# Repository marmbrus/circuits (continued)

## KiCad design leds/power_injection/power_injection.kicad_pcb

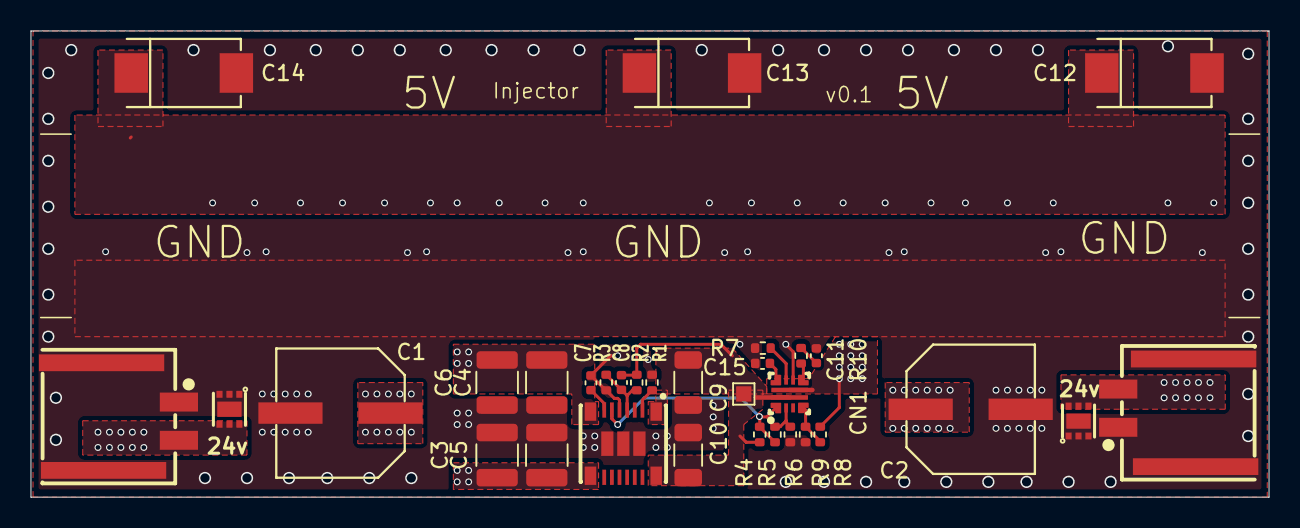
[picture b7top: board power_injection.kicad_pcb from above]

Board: 4 copper layers, 81.0 x 30.5 mm, 32 parts (0 on the bottom side), 14 nets.

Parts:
C1, C2: 220uF; CAP-SMD_BD8.0-L8.3-W8.3-FD
C3, C4, C5, C6: 10uF; C_1210_3225Metric
C7: 47nF; C_0402_1005Metric
C8: 47pF; C_0402_1005Metric
C9, C10: 10uF; C_1206_3216Metric
C11: 100nF; C_0402_1005Metric
C12, C13, C14: 330uF; CAP-SMD_L7.3-W4.3-FD
C15: 15nF; C_0402_1005Metric
CN1, CN2: 105430-1102; CONN-SMD_2P-P2.54_105430-1102
D5, D6: TVS2700DRVR; WSON-6_L2.0-W2.0-P0.65-BL-EP
R1: 162k; R_0402_1005Metric
R2: 73.2k; R_0402_1005Metric
R3: 10k; R_0402_1005Metric
R4: 470k; R_0402_1005Metric
R5: 45.3k; R_0402_1005Metric
R6: 147k; R_0402_1005Metric
R7: 562; R_0402_1005Metric
R8: 100k; R_0402_1005Metric
R9: 34k; R_0402_1005Metric
R10: 100; R_0402_1005Metric
TP1: TestPoint; TestPoint_Pad_1.0x1.0mm
U1: TPSM86837RCGR; B3QFN-19_L5.5-W5.0-P0.50-TL
U2: TPS259474LRPWR; VQFN-10_L2.0-W2.0-P0.45-TL

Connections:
/NanoFitPower/VIN: C1.1, C2.1, C3.1, C4.1, C5.1, C6.1, CN1.2, CN2.2, D5.4 (IN), D5.5 (IN), D5.6 (IN), D6.4 (IN), D6.5 (IN), D6.6 (IN), U1.8 (VIN), U1.9 (VIN)
/buck24v/5V_RAW: C8.1, C9.1, C10.1, R2.1, R4.1, TP1.1, U1.1 (VOUT), U1.16 (VOUT), U2.5 (IN)
/buck24v/VOUT: C12.1, C13.1, C14.1, R8.1, U2.6 (OUT)
GND: C1.2, C2.2, C3.2, C4.2, C5.2, C6.2, C7.2, C9.2, C10.2, C11.2, C12.2, C13.2, C14.2, C15.2, CN1.1, CN1.3, CN1.4, CN2.1, CN2.3, CN2.4, D5.1 (GND), D5.2 (GND), D5.3 (GND), D5.7 (GND), D6.1 (GND), D6.2 (GND), D6.3 (GND), D6.7 (GND), R1.2, R3.2, R6.2, R7.2, R9.2, U1.5 (AGND), U1.17 (PGND), U1.18 (PGND), U1.19 (PGND), U2.8 (GND)
unnamed: C11.1, R10.2
unnamed: C8.2, R2.2, R3.1, U1.4 (FB)
unnamed: R1.1, U1.2 (MODE)
unnamed: R4.2, R5.1, U1.6 (PG), U2.1 (EN/UVLO)
unnamed: C7.1, U1.7 (SS)
unnamed: R10.1, U2.7 (DVDT)
unnamed: R7.1, U2.9 (ILM)
unnamed: C15.1, U2.10 (ITIMER)
unnamed: R5.2, R6.1, U2.2 (OVLO/OVCSEL)
unnamed: R8.2, R9.1, U2.4 (PGTH/~FLT)

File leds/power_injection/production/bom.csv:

Designator,Footprint,Quantity,Value,LCSC Part #
"C1, C2",CAP-SMD_BD8.0-L8.3-W8.3-FD,2,220uF,C2923769
"C10, C9",1206,2,10uF,C2803389
C11,0402,1,100nF,
"C12, C13, C14",CAP-SMD_L7.3-W4.3-FD,3,330uF,C2159214
C15,0402,1,15nF,
"C3, C4, C5, C6",1210,4,10uF,C77102
C7,0402,1,47nF,
C8,0402,1,47pF,
"CN1, CN2",CONN-SMD_2P-P2.54_105430-1102,2,105430-1102,C2976139
"D5, D6",WSON-6_L2.0-W2.0-P0.65-BL-EP,2,TVS2700DRVR,C523797
R1,0402,1,162k,
R10,0402,1,100,
R2,0402,1,73.2k,
R3,0402,1,10k,
R4,0402,1,470k,
R5,0402,1,45.3k,
R6,0402,1,147k,
R7,0402,1,562,
R8,0402,1,100k,
R9,0402,1,34k,
TP1,TestPoint_Pad_1.0x1.0mm,1,TestPoint,
U1,B3QFN-19_L5.5-W5.0-P0.50-TL,1,TPSM86837RCGR,C34572614
U2,VQFN-10_L2.0-W2.0-P0.45-TL,1,TPS259474LRPWR,C2864845

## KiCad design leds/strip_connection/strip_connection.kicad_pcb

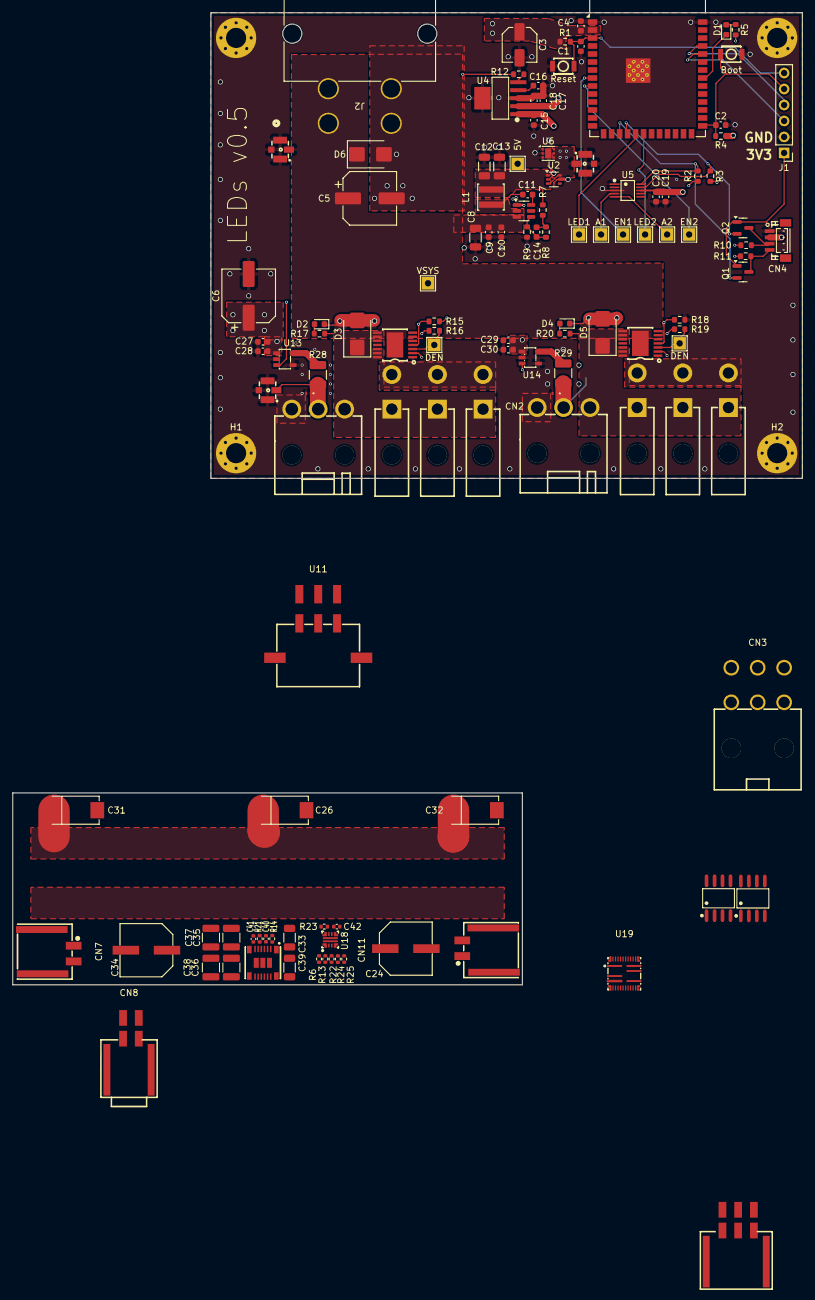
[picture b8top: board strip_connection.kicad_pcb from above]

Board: 4 copper layers, 125.5 x 154.5 mm, 127 parts (1 on the bottom side), 48 nets.

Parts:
C1: 10uf; C_0603_1608Metric
C2: 1uf; C_0603_1608Metric
C3: 22uF; C_Elec_5x5.8
C4, C10, C20, C28, C30: 100nF; C_0603_1608Metric
C5, C6: C_Polarized; CP_Elec_8x11.9
C8, C12, C13: 22uF; C_1206_3216Metric
C9, C27, C29: 10uF; C_0603_1608Metric
C11: 100nf; C_0603_1608Metric
C14: 75pF; C_0603_1608Metric
C15, C17, C18, C19: 1uF; C_0603_1608Metric
C16: 10nF; C_0603_1608Metric
C24, C34: 220uF; CAP-SMD_BD8.0-L8.3-W8.3-FD
C26, C31, C32: 330uF; CAP-SMD_L7.3-W4.3-FD
C33, C39: 10uF; C_1206_3216Metric
C35, C36, C37, C38: 10uF; C_1210_3225Metric
C40: 150pF; C_0402_1005Metric
C41, C42: 22nF; C_0402_1005Metric
CN1, CN2: 39303035; CONN-TH_39303035
CN3: 39301060; CONN-TN_39301060
CN4: BM04B-SRSS-TB(LF)(SN); CONN-SMD_BM04B-SRSS-TB
CN5, CN6, CN9, CN10, CN13, CN14: 39-30-1020; CONN-TH_2P-P5.50_39-30-1020
CN7, CN11: 105430-1102; CONN-SMD_2P-P2.54_105430-1102
CN8: 1054051104; CONN-SMD_1054051104
D1, D2, D4: LED; LED_0603_1608Metric
D3, D5, D6: D_TVS; D_SMB
H1, H2, H3, H4: MountingHole_Pad; MountingHole_3.2mm_M3_Pad_Via
J1: Conn_01x06; PinHeader_1x06_P2.54mm_Vertical
J2: 428202214; CONN_SDA-42820-0002_02_RC_MOL
L1: XAL4040-103MEC; IND-SMD_L4.0-W4.0-A
Q1, Q2: BSS138; SOT-23
R1, R2, R3, R4, R10, R11, R12: 10k; R_0603_1608Metric
R5: 330; R_0603_1608Metric
R6, R13, R14, R22, R23, R24, R25: 73.2k; R_0402_1005Metric
R7: 49.9; R_0603_1608Metric
R8: 100k; R_0603_1608Metric
R9: 13.3k; R_0603_1608Metric
R15, R18: 1.5k; R_0603_1608Metric
R16, R19: 4.7k; R_0603_1608Metric
R17, R20: 3.3k; R_0603_1608Metric
R21: 10k; R_0402_1005Metric
R28, R29: 120; R_1210_3225Metric_Pad1.30x2.65mm_HandSolder
RF1, RF2, RF3, RF4: 73412-0110; ANT-SMD_73412-0110
SW1, SW2: KEY-SMD_B3U-1000PM
TP1, TP2, TP3, TP4, TP5, TP7, TP9, TP14, TP15, TP16: LabeledTestPoint
U1: ESP32-S3-WROOM-1
U2: LM66100DCK; SOT-363_SC-70-6
U3: TPS54202DDC; SOT-23-6
U4: TPS73733DCQ_C5220270; SOT-223-6_L6.5-W3.5-P1.27-LS7.0-BR
U5: ADS1115IDGSR; MSOP-10_L3.0-W3.0-P0.50-LS5.0-BL
U6: TVS0500DRV; WSON-6-1EP_2x2mm_P0.65mm_EP1x1.6mm
U7, U10: TPD1E05U06DPY; Texas_DPY0002A_0.6x1mm_P0.65mm
U8, U9: BTS70021EPPXUMA1; PG-TSDSO-14_L4.9-W3.9-P0.65-LS6.0-BL-EP
U11: 430450609; CONN-SMD_6P-P3.0-H-R2-C3-S4.63
U12: 1054051106; CONN-SMD_1054051106
U13, U14: UCC27517DBVR; SOT-23-5_L3.0-W1.7-P0.95-LS2.8-BR
U15: TPSM86837RCGR; B3QFN-19_L5.5-W5.0-P0.50-TL
U16, U17: THVD2450DR; SOIC-8_L4.9-W3.9-P1.27-LS6.0-BL
U18: LM73100RPWR; VQFN-10_L2.0-W2.0-P0.45-TL
U19: MP5048GU-Z; QFN-30_L5.0-W5.0-P0.40-TL_MP5048GU-Z

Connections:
/3v3/3v3: C3.1, C4.1, C17.1, C18.1, J1.1, Q1.1 (G), Q2.1 (G), R1.1, R2.1, R3.1, R4.1, R5.2, U1.2 (3V3), U4.2 (OUT)
/5V: C6.1, C15.1, C19.1, C20.1, C27.1, C28.1, C29.1, C30.1, CN4.2, R10.1, R11.1, R12.1, R16.1, R19.1, RF2.2 (SIG), U2.3 (~CE), U2.6 (VOUT), U4.1 (IN), U5.8 (VDD), U6.4 (IN), U6.5 (IN), U6.6 (IN), U13.1 (VDD), U14.1 (VDD)
/NanoFitPower/VIN: C24.1, C34.1, C35.1, C36.1, C37.1, C38.1, CN7.2, CN11.2, U15.8 (VIN), U15.9 (VIN)
/VSYS: C5.1, C8.1, C9.1, C10.1, D6.1 (K), J2.1_1, J2.1_2, RF1.2 (SIG), TP1.1, U3.3 (VIN), U8.15 (VS), U9.15 (VS)
/a2d/AIN1: R15.1, TP4.1, U5.4 (AIN0), U8.4 (IS)
/a2d/AIN2: R18.1, TP5.1, U5.5 (AIN1), U9.4 (IS)
/a2d/I2C.SCL: Q1.2 (S), R2.2, U1.17 (IO9), U5.10 (SCL)
/a2d/I2C.SDA: Q2.2 (S), R3.2, U1.18 (IO10), U5.9 (SDA)
/buck24v/VOUT: C26.1, C31.1, C32.1, R24.1, U18.6 (OUT)
/buckconverter/FB: C14.1, R8.2, R9.1, U3.4 (FB)
/buckconverter/SW: C11.2, L1.1, U3.2 (SW)
/esp32/EN1: TP7.1, U1.8 (IO15), U8.2 (IN)
/esp32/EN2: TP9.1, U1.9 (IO16), U9.2 (IN)
/esp32/LED1: TP2.1, U1.19 (IO11), U13.3 (IN+)
/esp32/LED2: TP3.1, U1.20 (IO12), U14.3 (IN+)
/led_channel1/Switched12V: CN2.1, CN6.1, CN10.1, CN14.1, D5.1 (K), R20.1, U9.8 (OUT), U9.9 (OUT), U9.10 (OUT), U9.12 (OUT), U9.13 (OUT), U9.14 (OUT)
/led_channel/Switched12V: CN1.1, CN5.1, CN9.1, CN13.1, D3.1 (K), R17.1, U8.8 (OUT), U8.9 (OUT), U8.10 (OUT), U8.12 (OUT), U8.13 (OUT), U8.14 (OUT)
GND: C1.2, C2.2, C3.2, C4.2, C5.2, C6.2, C8.2, C9.2, C10.2, C12.2, C13.2, C15.2, C16.2, C17.2, C18.2, C19.2, C20.2, C27.2, C28.2, C29.2, C30.2, CN1.3, CN2.3, CN4.1, CN5.2, CN6.2, CN7.1, CN9.2, CN10.2, CN11.1, CN13.2, CN14.2, D2.1 (K), D3.2 (A), D4.1 (K), D5.2 (A), D6.2 (A), H1.1, H2.1, H3.1, H4.1, J1.2, J2.2_1, J2.2_2, R9.2, R15.2, R18.2, RF1.1 (GND), RF1.3 (GND), RF1.4 (GND), RF2.1 (GND), RF2.3 (GND), RF2.4 (GND), RF3.1 (GND), RF3.3 (GND), RF3.4 (GND), RF4.1 (GND), RF4.3 (GND), RF4.4 (GND), SW1.1, SW2.1, U1.1 (GND), U1.40 (GND), U1.41 (GND), U2.2 (GND), U2.5 (ST), U3.1 (GND), U4.3 (GND), U4.6 (GND), U5.1 (ADDR), U5.3 (GND), U6.1 (GND), U6.2 (GND), U6.3 (GND), U6.7 (GND), U7.2 (GND), U8.1 (GND), U9.1 (GND), U10.2 (GND), U13.2 (GND), U13.4 (IN-), U14.2 (GND), U14.4 (IN-)
unnamed: C14.2, R7.2, R8.1
unnamed: D1.2 (A), R5.1
unnamed: D1.1 (K), U1.33 (IO40)
unnamed: D2.2 (A), R17.2
unnamed: D4.2 (A), R20.2
unnamed: J1.3, U1.36 (RXD0)
unnamed: J1.4, U1.37 (TXD0)
unnamed: C2.1, J1.5, R4.2, SW2.2, U1.27 (IO0)
unnamed: C1.1, J1.6, R1.2, SW1.2, U1.3 (EN)
unnamed: CN4.4, Q1.3 (D), R11.2
unnamed: CN4.3, Q2.3 (D), R10.2
unnamed: CN1.2, R28.2, RF3.2 (SIG), U7.1 (I/O)
unnamed: CN2.2, R29.2, RF4.2 (SIG), U10.1 (I/O)
unnamed: C12.1, C13.1, L1.2, R7.1, TP14.1, U2.1 (VIN)
unnamed: C11.1, U3.6 (BOOT)
unnamed: R12.2, U4.5 (EN)
unnamed: C16.1, U4.4 (NR/FB)
unnamed: R16.2, TP15.1, U8.3 (DEN)
unnamed: R19.2, TP16.1, U9.3 (DEN)
unnamed: R28.1, U13.5 (OUT)
unnamed: R29.1, U14.5 (OUT)
unnamed: C24.2, C26.2, C31.2, C32.2, C33.2, C34.2, C35.2, C36.2, C37.2, C38.2, C39.2, C41.2, C42.2, R21.2, R22.2, R23.2, R25.2, U15.5 (AGND), U15.17 (PGND), U15.18 (PGND), U15.19 (PGND), U18.8 (GND)
unnamed: C40.2, R14.2, R21.1, U15.4 (FB)
unnamed: C41.1, U15.7 (SS)
unnamed: C42.1, U18.7 (DVDT)
unnamed: R6.2, R13.1, U18.1 (EN/UVLO)
unnamed: R23.1, U18.9 (IMON)
unnamed: C33.1, C39.1, C40.1, R6.1, R14.1, U15.1 (VOUT), U15.16 (VOUT), U18.5 (IN)
unnamed: R13.2, R22.1, U18.2 (OVLO)
unnamed: R24.2, R25.1, U18.4 (PGTH)

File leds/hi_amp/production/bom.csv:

Designator,Footprint,Quantity,Value,LCSC Part #
"C1, C21, C23, C25, C6, C9",0603,6,10uf,
"C10, C11, C20, C22, C24, C26, C4, C7",0603,8,100nF,
"C12, C13, C8",1206,3,22uF,
C14,0603,1,75pF,
"C15, C17, C18, C19, C2",0603,5,1uF,
C16,0603,1,10nF,
"C3, C5",C_Elec_5x5.8,2,22uF,C336246
"CN1, CN2",CONN-TH_0428192214,2,428192213,C563817
"CN10, CN11, CN12, CN14, CN15, CN16, CN18, CN19, CN20, CN6, CN7, CN8",CONN-TH_39288020,12,39288020,C490534
"CN13, CN17, CN5, CN9",CONN-TH_3P-P4.20_39302030,4,39302030,C589033
CN4,CONN-SMD_BM04B-SRSS-TB,1,BM04B-SRSS-TB(LF)(SN),C160390
D1,0603,1,LED,C2290
"D2, D4, D6, D8",0603,4,LED,C2286
"D3, D5, D7, D9",D_SMB,4,D_TVS,C151256
"FH1, FH10, FH11, FH12, FH13, FH14, FH15, FH16, FH2, FH3, FH4, FH5, FH6, FH7, FH8, FH9",FUSE-SMD_L9.8-W5.0_01550900M,16,01550900M,C108518
L1,IND-SMD_L4.0-W4.0_XAL4040-103,1,XGL4040-153MEC,C3911667
"Q1, Q2",SOT-23,2,BSS138,
"R1, R10, R11, R12, R2, R3, R4",0603,7,10k,
"R13, R14, R21, R6",0805,4,120,
"R15, R18, R22, R25",0603,4,1.5k,
"R16, R19, R23, R26",0603,4,4.7k,
"R17, R20, R24, R27",0603,4,3.3k,
R5,0603,1,330,
R7,0603,1,49.9,
R8,0603,1,100k,
R9,0603,1,13.3k,
"SW1, SW2",KEY-SMD_B3U-1000PM,2,KEY-SMD_B3U-1000PM,C231329
U1,ESP32-S3-WROOM-1,1,ESP32-S3-WROOM-1,
"U10, U2, U6, U7",SOT-23-5_L3.0-W1.7-P0.95-LS2.8-BR,4,UCC27517DBVR,C99395
"U11, U12, U8, U9",PG-TSDSO-14_L4.9-W3.9-P0.65-LS6.0-BL-EP,4,BTS70021EPPXUMA1,C2680407
U3,SOT-23-6,1,TPS54202DDC,
U4,SOT-223-6_L6.5-W3.5-P1.27-LS7.0-BR,1,TPS73733DCQ_C5220270,C5220270
U5,MSOP-10_L3.0-W3.0-P0.50-LS5.0-BL,1,ADS1115IDGSR,C37593

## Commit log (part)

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2024-07-02 first commit; laid out power protection
2024-07-02 more gitignore
2024-07-02 add protection schematic
2024-07-03 USBPowerMuxV0.3
2024-07-04 template files
2024-07-04 working on buck-boost
2024-07-04 drop powermux
2024-07-04 BuckBoostTest v0.1
2024-07-04 revisions
2024-07-05 reannotate
2024-07-10 add usb serial and start on ESP12
2024-07-11 esp basic layout
2024-07-11 add nested schematics
2024-07-12 add pins
2024-07-28 add easyeda libraries
2024-07-28 fix voltage divider
2024-07-28 clean up
2024-07-28 add LED jumper
2024-07-29 add meta
2024-07-29 add wago connector
2024-07-29 basic layout for flex power sensor
2024-07-29 more clean up
2024-07-29 add qwiic connector
2024-08-07 ready to fab
2024-08-08 move template
2024-08-09 preparing to fab a2d
2024-08-09 use 100nf
2024-08-09 fix large cap
2024-08-09 add second i2c connector
2024-11-02 usbpcb prototype
2024-11-16 a2d v0.2
2024-11-26 libraries for the surprise
2024-11-26 Surprise v0
2024-11-26 Fixes for REV20241126
2024-12-11 WIP: Revision2
2024-12-12 add parts
2024-12-12 add part numbers
2024-12-19 WIP: ESPIDF based surprise code
2024-12-19 new i2c driver
2024-12-19 new i2c driver, add support for more leds, enable 5v
2024-12-19 report battery status over mqtt
2024-12-19 add deepsleep after inactivity
2024-12-19 simple light pattern showing / recognizing
2024-12-20 better debouncing
2024-12-20 lots more patterns'
2024-12-21 add a bunch of different patterns
2024-12-21 movement interrupt working
2024-12-21 reporting orientation changes to the application/
2024-12-22 more mqtt messages
2024-12-22 Buttons light up when pressed.
2024-12-23 fix debouncing with active polling for dropped interrupts
2024-12-23 bring back wakeup button handling
2024-12-23 oritination based lights
2024-12-24 decrease brighness
2025-01-04 add easyeda components for espamp
2025-01-04 add resistor size reference guide
2025-01-04 add back i2c scanning
2025-01-04 update USB conector
2025-01-04 initial commit of espamp
2025-01-04 setup and route usbc pd
2025-01-05 fix config resistors, add test points, increase current handling vias/traces
2025-01-18 blank readme
2025-01-18 Update readme.md
    Basic readme
2025-01-18 Update readme.md
    Template setup.
2025-01-18 Initial usbserial design
2025-01-18 WIP: usbserial
2025-01-18 add some labels
2025-01-18 add inductor
2025-01-19 initial buckconverter with pcb
2025-01-19 cleanup usb serial
2025-01-25 usbserial 0.1 sent to fab
2025-01-26 fix via sizes
2025-01-28 Clean up the BOM - use whole numbers (.1uF -> 100nF) - capacitor voltage ratings ([22uF](https://jlcpcb.com/partdetail/PANASONIC-EEEFT1H220AR/C336246) at 50V)
2025-01-28 Add cap easyeda model)
2025-01-29 clean up layout
2025-02-19 add TPS73733
2025-02-19 more files
2025-02-19 work on usbserial
2025-03-02 amp schematic draft
2025-03-02 tweaks
2025-03-03 first draft of amp layout
2025-03-12 WIP: espamp
2025-03-13 amp schematic complete
2025-03-15 more work on espamp
2025-03-15 add RGBLED
2025-03-15 espamp v0.1
2025-03-18 usbserial v2
2025-03-19 reverse connector orientation for a2d
2025-03-30 First version of espamp software
2025-04-01 espamp revisions
2025-04-02 espamp v0.2
2025-04-02 minor fixes
2025-04-03 WIP: roomsensor
2025-04-05 more work on roomsensor
2025-04-05 add jst horizontal
2025-04-08 WIP: firmware for roomsensor
2025-04-08 code reorg
2025-04-14 more work on sensor code
2025-04-15 update pins
2025-04-15 update to use light grid
2025-04-15 add light patterns
2025-04-16 roomsensor v2.0
2025-04-17 i2c polling framework
2025-04-18 add device tats
2025-04-19 add more sensors and mqtt reporting
2025-04-19 metrics endpoint, limit interrupt polling
2025-04-19 add http code, improve intrrupt ratelimiting / polling
2025-04-19 remove spurious warnings
2025-04-19 WIP: OTA
2025-04-19 OTA Checks
2025-04-19 WIP: OTA checks
2025-04-19 timezone fixes
2025-04-19 remove the test
2025-04-20 polling OTA
2025-04-20 WIP: periodic checks
2025-04-20 WIP: ota mqtt reports
2025-04-20 cursor rules
2025-04-20 OTA race conditions
2025-04-22 mqtt cleanup
2025-05-06 sensor v2.1
2025-05-06 more parts
2025-05-07 v2.1
2025-07-10 new parts
2025-07-10 DRAFT: led controller
2025-07-11 first draft
2025-07-11 First revision of LEDs sent to fab
2025-07-18 a2d v0.4
2025-07-18 more lcsc components
2025-07-18 window controller v0.1
2025-07-18 more tweaking
2025-08-13 Fix errors in LEDs. Revision 0.2 ready to fab.
    - [x] Connect VCC on level shifter
    - [x] Connect DEN with pull-up
    - [x] Add channel on indicator LED - 3.3k
    - [x] Flip 3 pin connector
    - [x] 82 ohm damping resistor on LED drivers
    - [x] Add status LED - white 220 - sinking to ESP
2025-08-13 hacks for LED controller
2025-08-15 WIP: very basic rainbow LEDs
2025-08-17 WIP: new configuration system
2025-08-17 WIP: Basic LED rewrite.
2025-08-19 improvments to wifi and status display
2025-08-19 faster led bounce
2025-08-19 add lux sensor driver
2025-08-19 remove old lights subsystem
2025-08-19 add iomux initial implementation
2025-08-19 window controller v2
2025-08-19 add io expander sub system
2025-08-20 add support for motion detection
2025-08-21 more robust wifi setup / errors
2025-08-21 switching to https for ota deployment
2025-08-21 WIP: improve ota
2025-08-22 Add serving to webapp, game of life
2025-08-22 add a simple webapp
2025-08-22 status heartbeat display
2025-08-22 clean up mqtt connection handling
2025-08-22 improvements to IO and a2d configuration
2025-08-22 add retained boot telemetry to webapp
2025-08-23 improve boot telemetry
2025-08-23 add logging to mqtt
2025-08-23 metric timestamps
2025-08-23 dynamic mqtt configuration
2025-08-23 WIP: js OTA
2025-08-23 Add support for WS2814 WRGB
2025-08-23 Fix color mapping
2025-08-24 add duty cycle control
2025-08-24 WIP: fixing OTA
2025-08-24 Implement clean version format: git hash for clean builds, revYYYYMMDDHHMMSS-shortHash-dirty for dirty builds
    - Store the correct format from the beginning instead of extracting later
    - CMakeLists.txt: Use git hash for PROJECT_VER on clean builds
    - deploy_ota.sh: Use git hash in manifest for clean builds
    - Removed all hash extraction logic from ota.cpp
    - Consistent version reporting across firmware, web, local, and remote
2025-08-24 Revert "add duty cycle control"
    This reverts commit 5d6d4d8dd90bd5e24554717fda3a58de7b414bfa.
2025-08-24 fix led sliders
2025-08-27 add gpio control to serial console
2025-08-27 WIP: refactor LEDs to abstract color order and grid layout from patterns
2025-08-27 WIP: flip dot support
2025-08-27 tweak power monitoring constants
2025-08-27 version summary
2025-08-27 calibrate amps, fix polarity of IO, better logging and layout
2025-08-29 mqtt reconnection, jump to sensors with errors
2025-08-29 WIP: dynamic song selection
2025-08-29 more logging
2025-08-29 more logging of amp state
2025-08-29 basic sandstorm streaming
2025-08-29 add sdkconfig.defaults
2025-08-29 mutiple song stop/start
2025-08-29 Finally fix the encoding
2025-08-30 new 47uF cap
2025-08-31 roomsenor v2.2
2025-08-31 roomsenor v2.2 more changes
2025-09-01 more robust startup with bad wifi, print mac/ip on start, fix initial state of mcp switches
2025-09-02 more js tweaks
2025-09-02 fix LWT
2025-09-02 add restart topic/button
2025-09-02 add names to leds
2025-09-03 WIP: fix init time at led power on
2025-09-03 WIP: LED cleanup
2025-09-03 simple fade
2025-09-03 clock fixes
2025-09-03 wait for data to be ready
2025-09-03 granular led power
2025-09-03 granular led chasing
2025-09-03 clean up logging and warm up before sensor reporting
2025-09-04 fix sen55 temp readings
2025-09-04 WIP: temp connector board
2025-09-05 add contact and switch status to config
2025-09-05 update js
2025-09-05 add jst sen55 connector
2025-09-05 add old system temp connectors
2025-09-05 add LMP91000
2025-09-05 add serpentine column major
2025-09-05 WIP: air quality addition
2025-09-06 first version of air sensor
2025-09-06 more sen55 logging
2025-09-06 air add on v0.1
2025-09-08 smaller inductor
2025-09-08 first version of lock controller
2025-09-08 Add AMG8833
2025-09-08 last tweaks to locks
2025-09-08 quiet probe logging
2025-09-08 Revert "quiet probe logging"
    This reverts commit d58dd1a655596262fea92ba6a8ea079c392d4308.
2025-09-08 Revert "Add AMG8833"
    This reverts commit 33a2e2831a3572a5d341268e176c1111f6ee5141.
2025-09-09 reboot all button
2025-09-09 use external ram for tls
2025-09-09 move large LED allcations to ram
2025-09-09 WIP: fixing ota with lots of LEDs
2025-09-10 Revert "move large LED allcations to ram"
    This reverts commit 1aedee625211b2d0b757f0df1a3f0bd99b54e9f0.
2025-09-11 passes one round of manual tests
2025-09-11 fix web update status
2025-09-11 add simple status led
2025-09-12 add a new testing framework and use it to create a more robust provisioning tool. Use more of 16mb in partition table. Make the serial console simpler and add tty command for friendly mode
2025-09-12 add clone sensor
2025-09-12 led config
2025-09-12 add ota integration test
2025-09-12 led version configurations
2025-09-13 Add support for high/low switches. Device local logic for keypad overrides.
2025-09-14 add door lock override logic
2025-09-19 air v0.2
2025-09-30 support for i2c drivers on the same address
2025-09-30 WIP: CO sensor
2025-10-01 Test OTA
2025-10-03 add molex minifit sr horiz connector
2025-10-03 UHP200 Connector Prototype
2025-10-03 create hi amp led project. remove duplicate src dir
2025-10-03 add molex minifit sr virt
2025-10-04 WIP hi_amp leds
2025-10-07 WIP: add vias to buck (after fabrication).
2025-10-11 add more vias and send hi_amp to fab
2025-10-14 WIP: initial cut at moisture sensor
2025-10-14 add 6pin jst
2025-10-14 add game of life stats
2025-10-14 WIP roomsensor 2.3
2025-10-20 roomsensor v2.3
2025-10-27 add stronger gate driver to LEDs
2025-11-03 clean up led vias
2025-11-08 Support for multiple LED enable pins, Support for game of life start seeds and RLE patterns using new life configuration module
2025-11-08 remove comments
2025-11-09 multi module serpentine column major
2025-11-09 add summary pattern
2025-11-15 WIP: Henry
2025-11-15 add args to provision script
2025-11-15 fix js
2025-11-15 more patterns, revert transitions
2025-11-17 add more patterns
2025-11-29 Add metrics, and change RMT to a custom implmentation
2025-11-30 WIP: uhp500 conn
2025-11-30 More patterns, font fixes
2025-12-08 WIP: leds low_profile
2025-12-16 Low profile LED controller
2025-12-19 WIP: LEDS V2
2025-12-19 First draft of power injector
2025-12-20 power injection v0.1
2025-12-28 add marquee pattern
2025-12-28 UHP500 V1
2025-12-28 final tweaks
2025-12-28 inline the LED strip RMT adapter from managed componenets. Slow down the sk6812 protocol
2026-01-01 receiver v0.1
2026-01-01 high speed controler v2.0
2026-01-08 Small RGBYWW strip v0.1
2026-01-10 happy new year mode
2026-01-20 update non-standard LED foot prints
2026-01-23 slow fades
2026-01-23 add commands for controlling leds directly and a script for calibration
2026-01-23 HACK: support 8mb chip
2026-01-23 WIP: test program for hd108
2026-01-23 initial refactoring
2026-01-23 WIP: first draft of hd108 integration
2026-01-23 remove spurious changes
2026-01-23 remove hd108 test
2026-02-08 high-speed v2.1 fab
2026-02-11 lamp initial design
2026-02-23 WIP: Lamp
2026-03-04 Lamp v0.1 Fabrication
2026-06-20 Configure standard I2S format for MAX98357 chip and fix ESP-ADF build errors
